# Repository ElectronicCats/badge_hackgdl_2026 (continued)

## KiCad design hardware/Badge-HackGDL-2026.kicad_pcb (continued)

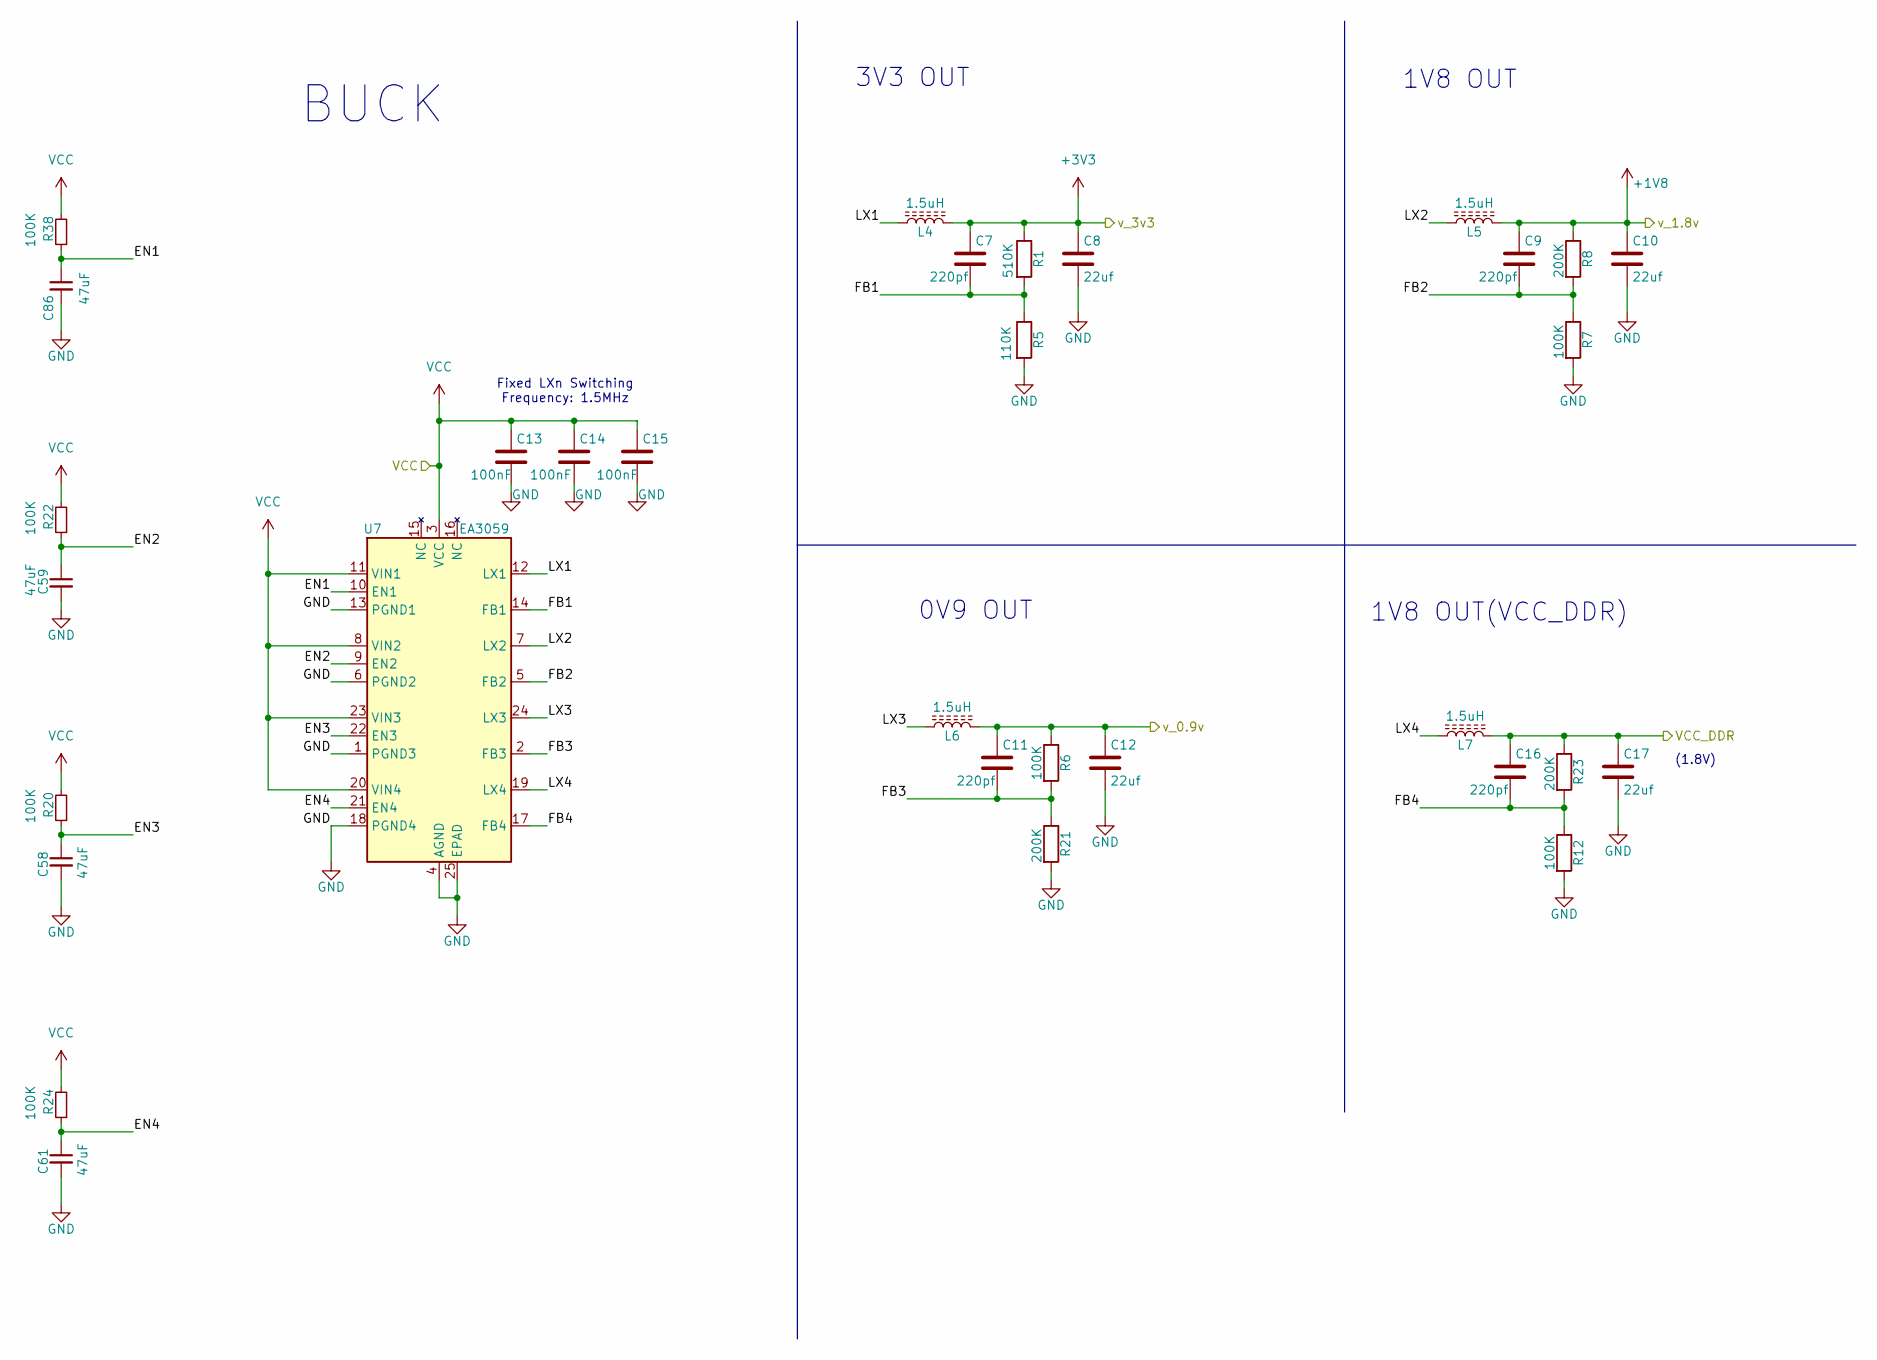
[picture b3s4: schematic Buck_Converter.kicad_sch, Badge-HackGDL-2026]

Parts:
C7, C9, C11, C16: 220pf; C_0402_1005Metric; LCSC# C107001
C8, C10, C12, C17: 22uf; C_0402_1005Metric; LCSC# C415703
C13, C14, C15: 100nF; C_0402_1005Metric; LCSC# C77020
C58, C59, C61, C86: 47uF; C_0603_1608Metric; LCSC# C140782
L4, L5, L6, L7: 1.5uH; L_1008_2520Metric; LCSC# C7427193
R1: 510K; R_0402_1005Metric; LCSC# C365024
R5: 110K; R_0402_1005Metric; LCSC# C2909311
R6, R7, R12, R20, R22, R24, R38: 100K; R_0402_1005Metric; LCSC# C844674
R8, R21, R23: 200K; R_0402_1005Metric; LCSC# C364966
U7: EA3059; VQFN-24-1EP_4x4mm_P0.5mm_EP2.5x2.5mm; LCSC# C111586

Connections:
+1V8: C9.1, C10.1, L5.2, R8.1; also elsewhere on the board
+3V3: C7.1, C8.1, L4.2, R1.1; also elsewhere on the board
/Buck_Converter/EN1: C86.1, R38.1, U7.10 (EN1)
/Buck_Converter/EN2: C59.1, R22.1, U7.9 (EN2)
/Buck_Converter/EN3: C58.1, R20.1, U7.22 (EN3)
/Buck_Converter/EN4: C61.1, R24.1, U7.21 (EN4)
/Buck_Converter/FB1: C7.2, R1.2, R5.1, U7.14 (FB1)
/Buck_Converter/FB2: C9.2, R7.1, R8.2, U7.5 (FB2)
/Buck_Converter/FB3: C11.2, R6.2, R21.1, U7.2 (FB3)
/Buck_Converter/FB4: C16.2, R12.1, R23.2, U7.17 (FB4)
/Buck_Converter/LX1: L4.1, U7.12 (LX1)
/Buck_Converter/LX2: L5.1, U7.7 (LX2)
/Buck_Converter/LX3: L6.1, U7.24 (LX3)
/Buck_Converter/LX4: L7.1, U7.19 (LX4)
/Buck_Converter/VCC_DDR: C16.1, C17.1, L7.2, R23.1; also elsewhere on the board
/MCU/VDD_ARM: C11.1, C12.1, L6.2, R6.1; also elsewhere on the board
GND: C8.2, C10.2, C12.2, C13.2, C14.2, C15.2, C17.2, C58.2, C59.2, C61.2, C86.2, R5.2, R7.2, R12.2, R21.2, U7.1 (PGND3), U7.4 (AGND), U7.6 (PGND2), U7.13 (PGND1), U7.18 (PGND4), U7.25 (EPAD); also elsewhere on the board
VCC: C13.1, C14.1, C15.1, R20.2, R22.2, R24.2, R38.2, U7.3 (VCC), U7.8 (VIN2), U7.11 (VIN1), U7.20 (VIN4), U7.23 (VIN3); also elsewhere on the board

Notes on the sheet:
Fixed LXn Switching Frequency: 1.5MHz
1V8 OUT(VCC_DDR)
1V8 OUT
(1.8V)
BUCK
0V9 OUT
3V3 OUT

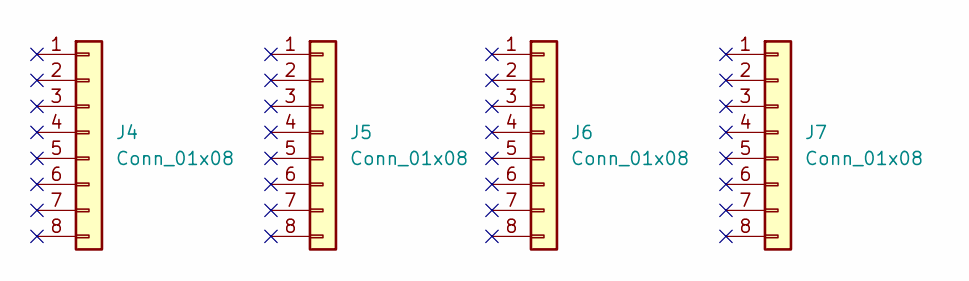
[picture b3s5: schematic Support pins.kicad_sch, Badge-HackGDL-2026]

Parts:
J4, J5, J6, J7: Conn_01x08; PinSocket_1x08_P2.54mm_Vertical; LCSC# C5224027

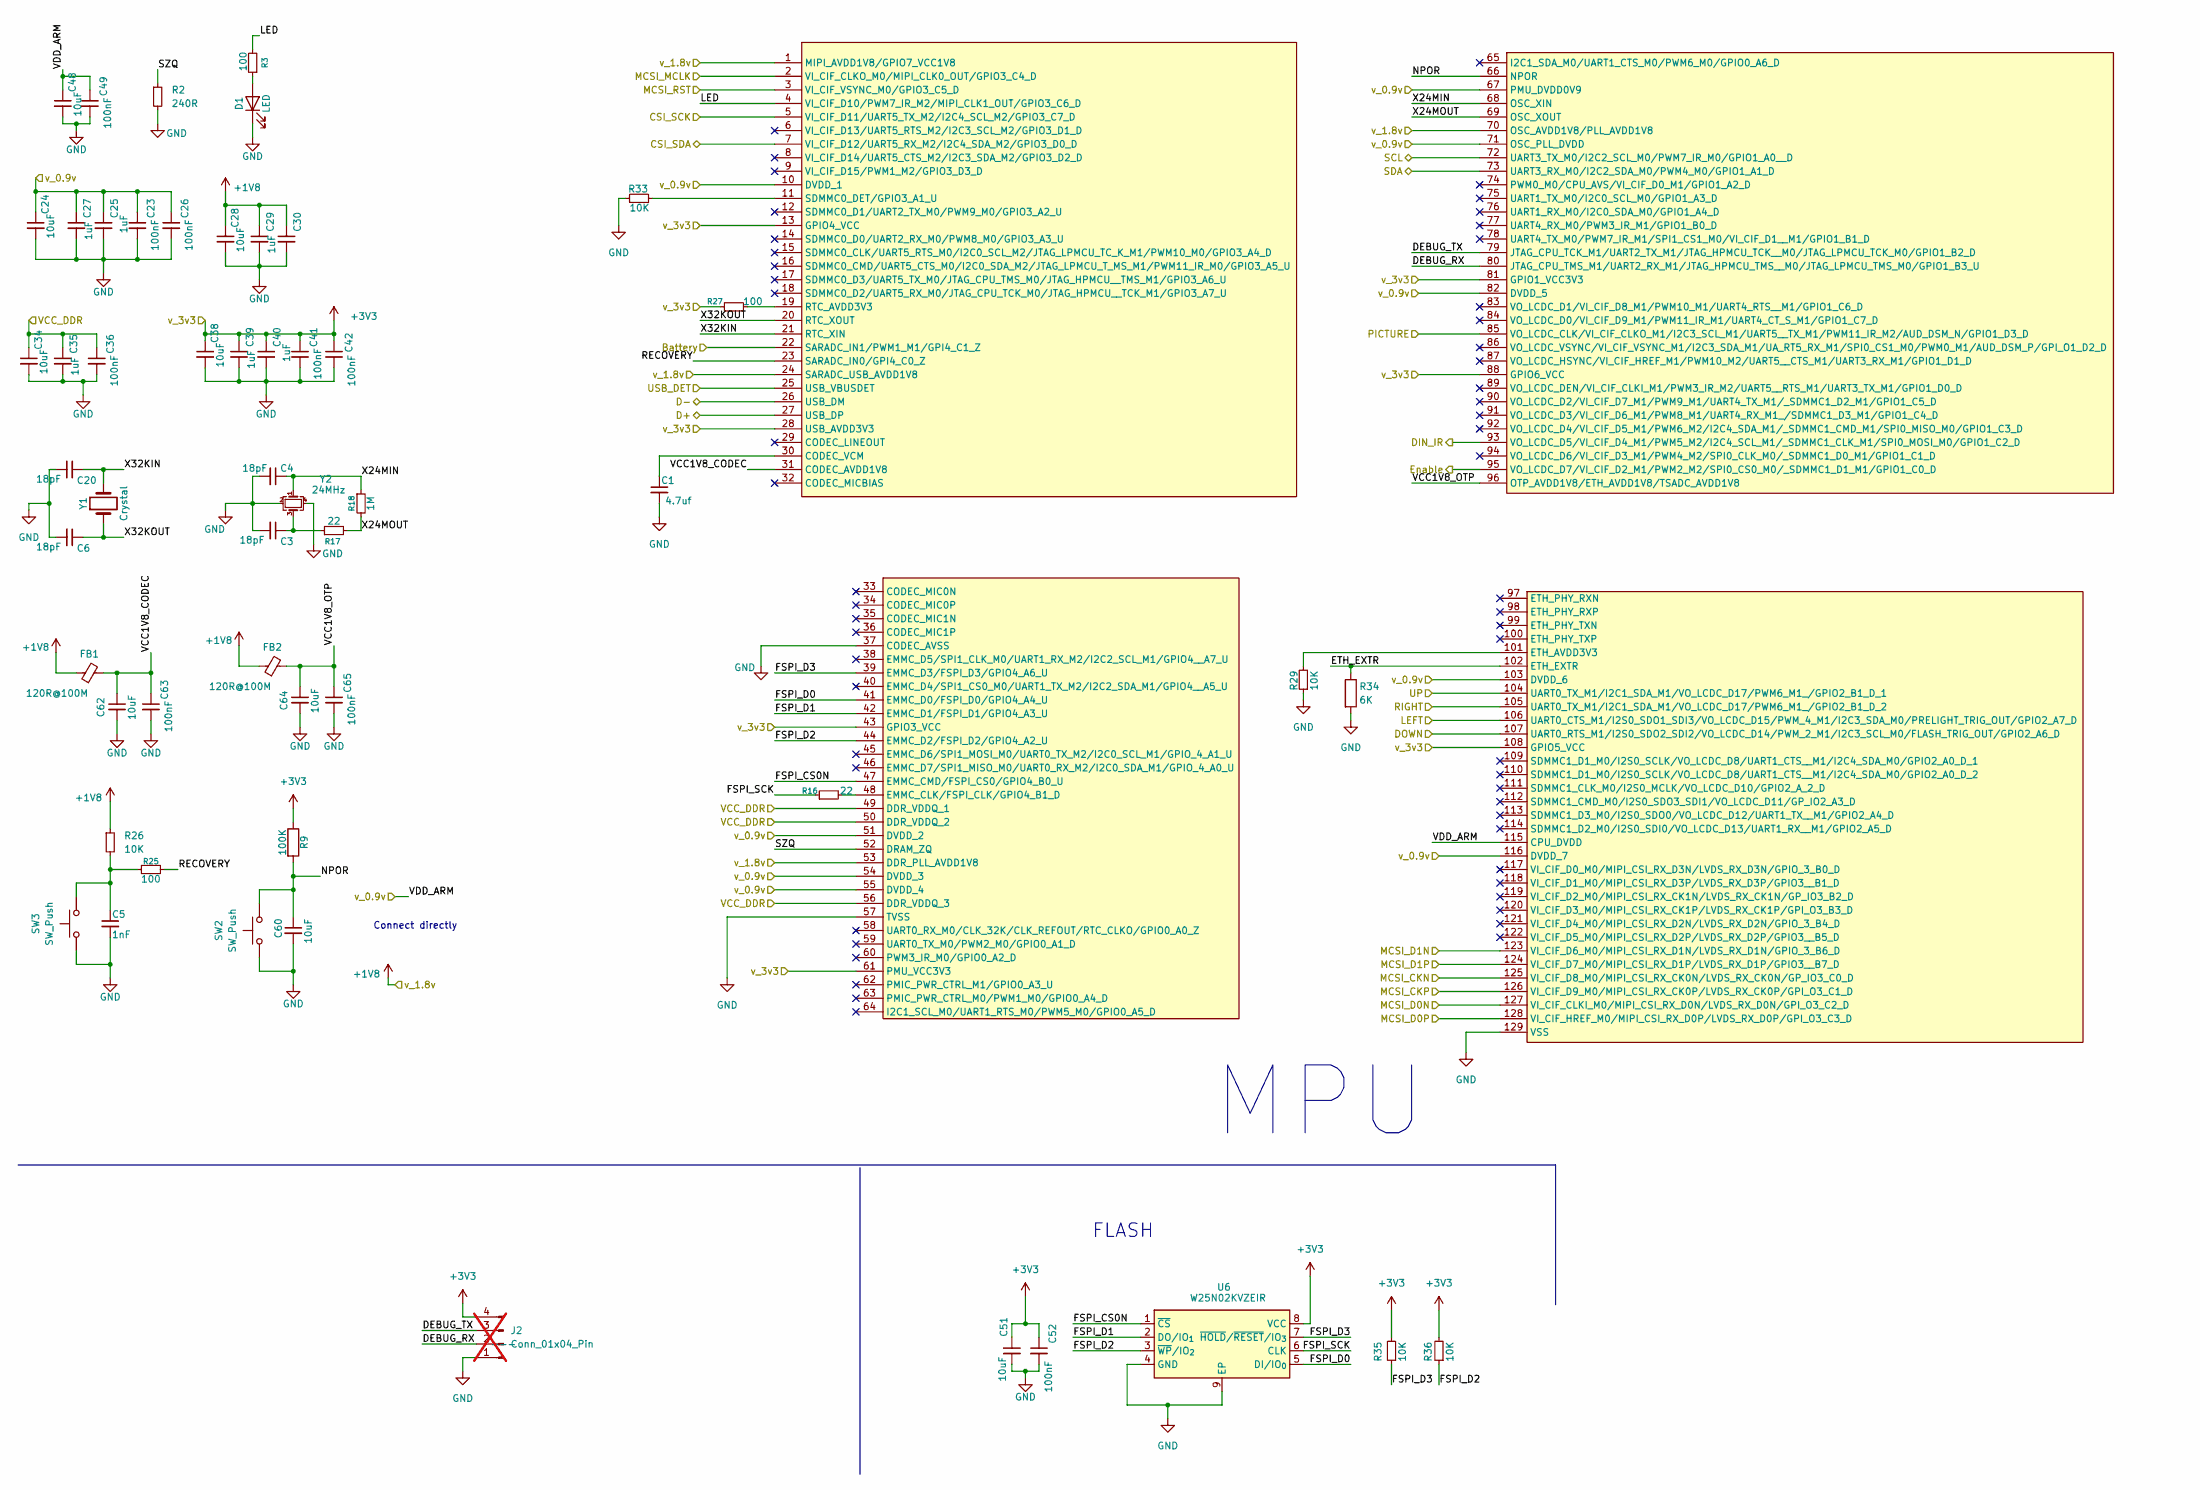
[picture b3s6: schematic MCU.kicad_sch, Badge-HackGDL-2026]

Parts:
C1: 4.7uf; C_0402_1005Metric; LCSC# C6119795
C3, C4, C6, C20: 18pF; C_0402_1005Metric; LCSC# C161534
C5: 1nF; C_0402_1005Metric; LCSC# C189467
C23, C26, C36, C41, C42, C49, C52, C63, C65: 100nF; C_0402_1005Metric; LCSC# C77020
C24, C28, C34, C38, C48, C51, C62, C64: 10uF; C_0402_1005Metric; LCSC# C7472949
C25, C27, C29, C30, C35, C39, C40: 1uF; C_0402_1005Metric; LCSC# C52923
C60: 10uF; C_0603_1608Metric; LCSC# C96446
D1: LED; LED_0603_1608Metric; LCSC# C22371297
FB1, FB2: 120R@100M; L_0603_1608Metric; LCSC# C14709
J2: Conn_01x04_Pin; 4 Pin 2.54mm; not fitted
R2: 240R; R_0402_1005Metric; LCSC# C25094
R3, R25, R27: 100; R_0402_1005Metric; LCSC# C2906860
R9: 100K; R_0402_1005Metric; LCSC# C844674
R16, R17: 22; R_0402_1005Metric; LCSC# C159964
R18: 1M; R_0402_1005Metric; LCSC# C131492
R26, R29, R33, R35, R36: 10K; R_0402_1005Metric; LCSC# C2759535
R34: 6K; R_0805_2012Metric; LCSC# C2828725
SW2, SW3: SW_Push; SW_SPST_TL3342; LCSC# C318889
U6: W25N02KVZEIR; WSON-8-1EP_8x6mm_P1.27mm_EP3.4x4.3mm; LCSC# C3010298
U8: RV1106G3; LCSC# C5328706
Y1: Crystal; Crystal_SMD_3215-2Pin_3.2x1.5mm; LCSC# C620155
Y2: 24MHz; Crystal_SMD_3225-4Pin_3.2x2.5mm; LCSC# C70590

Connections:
+1V8: C28.1, C29.1, C30.1, FB1.1, FB2.1, R26.1, U8.1 (MIPI_AVDD1V8/GPIO7_VCC1V8), U8.24 (SARADC_USB_AVDD1V8), U8.53 (DDR_PLL_AVDD1V8), U8.70 (OSC_AVDD1V8/PLL_AVDD1V8); also elsewhere on the board
+3V3: C38.1, C39.1, C40.1, C41.1, C42.1, C51.1, C52.1, J2.4, R9.1, R27.1, R35.2, R36.2, U6.8 (VCC), U8.13 (GPIO4_VCC), U8.28 (USB_AVDD3V3), U8.43 (GPIO3_VCC), U8.61 (PMU_VCC3V3), U8.81 (GPIO1_VCC3V3), U8.88 (GPIO6_VCC), U8.108 (GPIO5_VCC); also elsewhere on the board
/Buck_Converter/VCC_DDR: C34.1, C35.1, C36.1, U8.49 (DDR_VDDQ_1), U8.50 (DDR_VDDQ_2), U8.56 (DDR_VDDQ_3); also elsewhere on the board
/Cam/CSI_SCK: U8.5 (VI_CIF_D11/UART5_TX_M2/I2C4_SCL_M2/GPIO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); also elsewhere on the board
/Cam/CSI_SDA: U8.7 (VI_CIF_D12/UART5_RX_M2/I2C4_SDA_M2/GPIO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); also elsewhere on the board
/Cam/MCSI_CKN: U8.125 (VI_CIF_D8_M0/MIPI_CSI_RX_CK0N/LVDS_RX_C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); also elsewhere on the board
/Cam/MCSI_CKP: U8.126 (VI_CIF_D9_M0/MIPI_CSI_RX_CK0P/LVDS_RX_C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); also elsewhere on the board
/Cam/MCSI_D0N: U8.127 (VI_CIF_CLKI_M0/MIPI_CSI_RX_D0N/LVDS_RX_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); also elsewhere on the board
/Cam/MCSI_D0P: U8.128 (VI_CIF_HREF_M0/MIPI_CSI_RX_D0P/LVDS_RX_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); also elsewhere on the board
/Cam/MCSI_D1N: U8.123 (VI_CIF_D6_M0/MIPI_CSI_RX_D1N/LVDS_RX_D1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); also elsewhere on the board
/Cam/MCSI_D1P: U8.124 (VI_CIF_D7_M0/MIPI_CSI_RX_D1P/LVDS_RX_D1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); also elsewhere on the board
/Cam/MCSI_MCLK: U8.2 (VI_CIF_CLKO_M0/MIPI_CLK0_OUT/GPIO3_C4_D); also elsewhere on the board
/Cam/MCSI_RST: U8.3 (VI_CIF_VSYNC_M0/GPIO3_C5_D); also elsewhere on the board
/MCU/Battery: U8.22 (SARADC_IN1/PWM1_M1/GPI4_C1_Z); also elsewhere on the board
/MCU/D+: U8.27 (USB_DP); also elsewhere on the board
/MCU/D-: U8.26 (USB_DM); also elsewhere on the board
/MCU/DEBUG_RX: J2.2, U8.80 (JTAG_CPU_TMS_M1/UART2_RX_M1/JTAG_HPMCU_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)
/MCU/DEBUG_TX: J2.3, U8.79 (JTAG_CPU_TCK_M1/UART2_TX_M1/JTAG_HPMCU_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)
/MCU/DIN_IR: U8.93 (VO_LCDC_D5/VI_CIF_D4_M1/PWM5_M2/I2C4_SC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); also elsewhere on the board
/MCU/DOWN: U8.107 (UART0_RTS_M1/I2S0_SDO2_SDI2/VO_LCDC_D14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); also elsewhere on the board
/MCU/ETH_EXTR: R34.1, U8.102 (ETH_EXTR)
/MCU/Enable: U8.95 (VO_LCDC_D7/VI_CIF_D2_M1/PWM2_M2/SPI0_CS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); also elsewhere on the board
/MCU/FSPI_CS0N: U6.1 (~CS), U8.47 (EMMC_CMD/FSPI_CS0/GPIO4_B0_U)
/MCU/FSPI_D0: U6.5 (DI/IO_{0}), U8.41 (EMMC_D0/FSPI_D0/GPIO4_A4_U)
/MCU/FSPI_D1: U6.2 (DO/IO_{1}), U8.42 (EMMC_D1/FSPI_D1/GPIO4_A3_U)
/MCU/FSPI_D2: R36.1, U6.3 (~WP/IO_{2}), U8.44 (EMMC_D2/FSPI_D2/GPIO4_A2_U)
/MCU/FSPI_D3: R35.1, U6.7 (~HOLD/~RESET/IO_{3}), U8.39 (EMMC_D3/FSPI_D3/GPIO4_A6_U)
/MCU/FSPI_SCK: R16.1, U6.6 (CLK)
/MCU/LED: R3.2, U8.4 (VI_CIF_D10/PWM7_IR_M2/MIPI_CLK1_OUT/GPI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)
/MCU/LEFT: U8.106 (UART0_CTS_M1/I2S0_SDO1_SDI3/VO_LCDC_D15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); also elsewhere on the board
/MCU/NPOR: C60.1, R9.2, SW2.2, U8.66 (NPOR)
/MCU/PICTURE: U8.85 (VO_LCDC_CLK/VI_CIF_CLKO_M1/I2C3_SCL_M1/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); also elsewhere on the board
/MCU/RECOVERY: R25.2, U8.23 (SARADC_IN0/GPI4_C0_Z)
/MCU/RIGHT: U8.105 (UART0_TX_M1/I2C1_SDA_M1/VO_LCDC_D17/PWM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); also elsewhere on the board
/MCU/SCL: U8.72 (UART3_TX_M0/I2C2_SCL_M0/PWM7_IR_M0/GPIO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); also elsewhere on the board
/MCU/SDA: U8.73 (UART3_RX_M0/I2C2_SDA_M0/PWM4_M0/GPIO1_A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); also elsewhere on the board
/MCU/SZQ: R2.1, U8.52 (DRAM_ZQ)
/MCU/UP: U8.104 (UART0_TX_M1/I2C1_SDA_M1/VO_LCDC_D17/PWM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); also elsewhere on the board
/MCU/USB_DET: U8.25 (USB_VBUSDET); also elsewhere on the board
/MCU/VCC1V8_CODEC: C62.1, C63.1, FB1.2, U8.31 (CODEC_AVDD1V8)
/MCU/VCC1V8_OTP: C64.1, C65.1, FB2.2, U8.96 (OTP_AVDD1V8/ETH_AVDD1V8/TSADC_AVDD1V8)
/MCU/VDD_ARM: C23.1, C24.1, C25.1, C26.1, C27.1, C48.1, C49.1, U8.10 (DVDD_1), U8.51 (DVDD_2), U8.54 (DVDD_3), U8.55 (DVDD_4), U8.67 (PMU_DVDD0V9), U8.71 (OSC_PLL_DVDD), U8.82 (DVDD_5), U8.103 (DVDD_6), U8.115 (CPU_DVDD), U8.116 (DVDD_7); also elsewhere on the board
/MCU/X24MIN: C4.1, R18.1, U8.68 (OSC_XIN), Y2.1
/MCU/X24MOUT: R17.2, R18.2, U8.69 (OSC_XOUT)
/MCU/X32KIN: C20.1, U8.21 (RTC_XIN), Y1.2
/MCU/X32KOUT: C6.1, U8.20 (RTC_XOUT), Y1.1
GND: C1.2, C3.2, C4.2, C5.2, C6.2, C20.2, C23.2, C24.2, C25.2, C26.2, C27.2, C28.2, C29.2, C30.2, C34.2, C35.2, C36.2, C38.2, C39.2, C40.2, C41.2, C42.2, C48.2, C49.2, C51.2, C52.2, C60.2, C62.2, C63.2, C64.2, C65.2, D1.1 (K), J2.1, R2.2, R29.1, R33.1, R34.2, SW2.1, SW3.1, U6.4 (GND), U6.9 (EP), U8.37 (CODEC_AVSS), U8.57 (TVSS), U8.129 (VSS), Y2.2, Y2.4; also elsewhere on the board
unnamed: C3.1, R17.1, Y2.3
unnamed: C5.1, R25.1, R26.2, SW3.2
unnamed: D1.2 (A), R3.1
unnamed: C1.1, U8.30 (CODEC_VCM)
unnamed: R27.2, U8.19 (RTC_AVDD3V3)
unnamed: R33.2, U8.11 (SDMMC0_DET/GPIO3_A1_U)
unnamed: R16.2, U8.48 (EMMC_CLK/FSPI_CLK/GPIO4_B1_D)
unnamed: R29.2, U8.101 (ETH_AVDD3V3)

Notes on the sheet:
FLASH
Connect directly
MPU

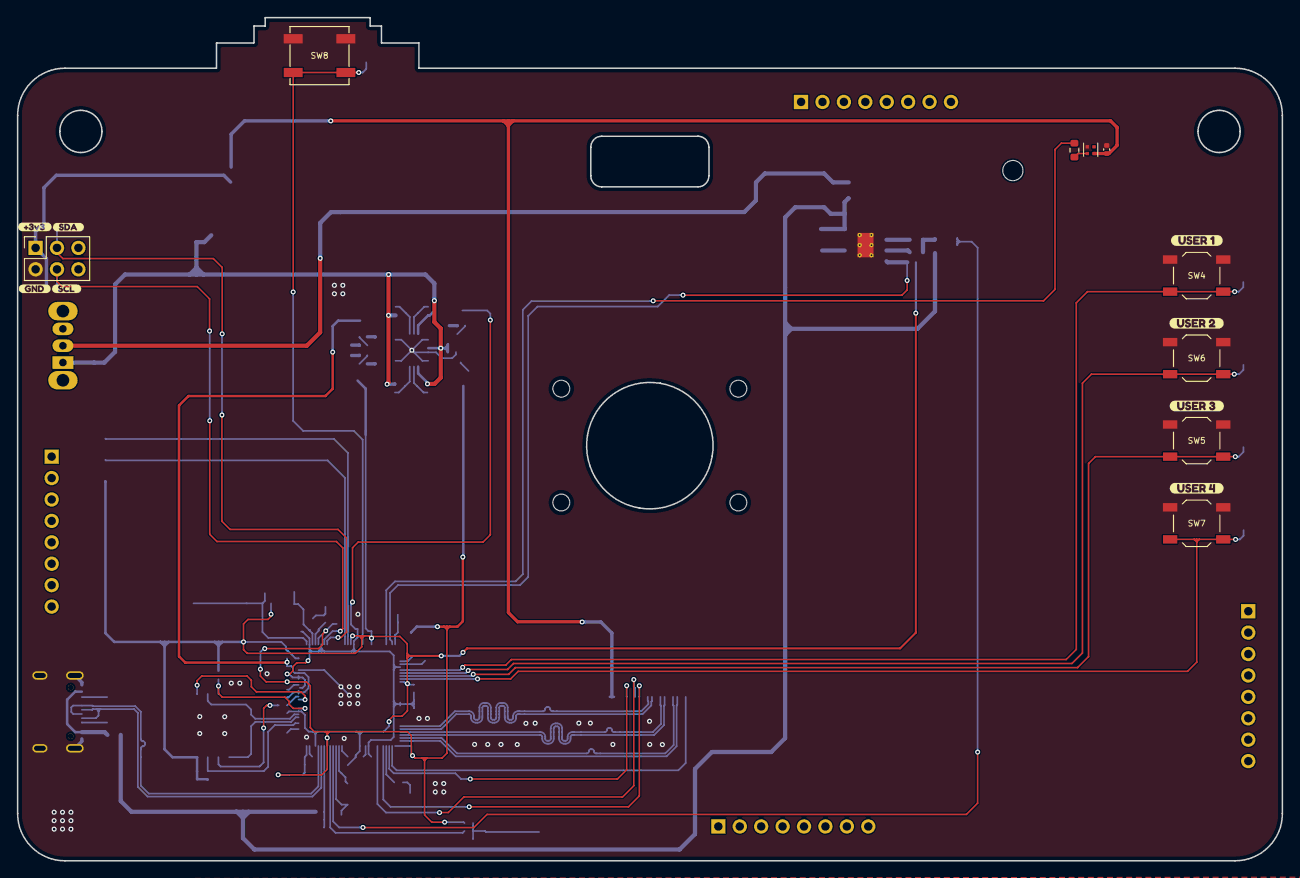
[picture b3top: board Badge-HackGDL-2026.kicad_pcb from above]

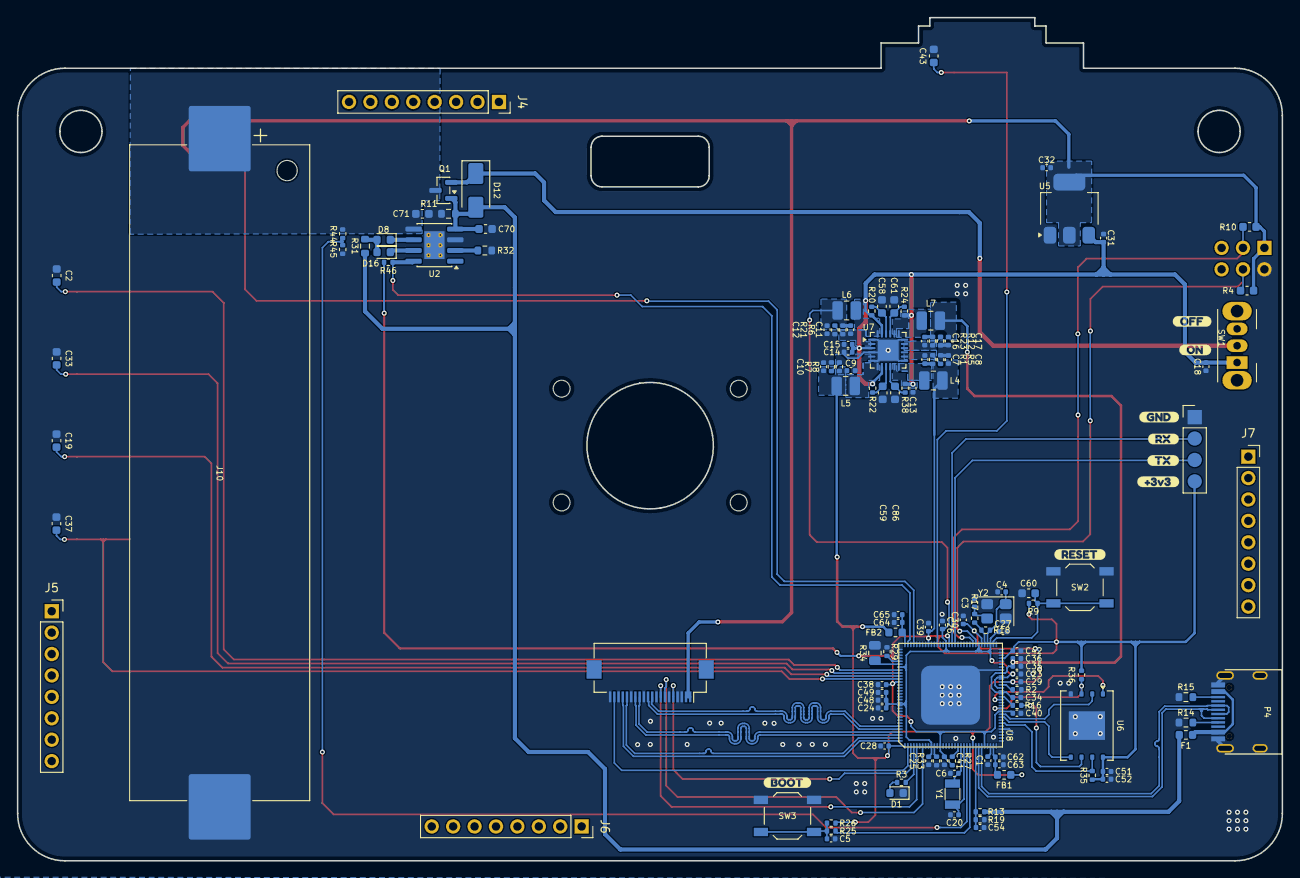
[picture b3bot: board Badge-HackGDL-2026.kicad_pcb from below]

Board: 2 copper layers, 150.0 x 100.0 mm, 151 parts (133 on the bottom side), 80 nets.

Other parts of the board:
kibuzzard-684B03BD: G***; kibuzzard-684B03BD
kibuzzard-684B03C9: G***; kibuzzard-684B03C9
kibuzzard-684B03D5: G***; kibuzzard-684B03D5
kibuzzard-69714B9C: G***; kibuzzard-69714B9C
kibuzzard-69714BBC: G***; kibuzzard-69714BBC
kibuzzard-69714BDE: G***; kibuzzard-69714BDE
kibuzzard-69714C02: G***; kibuzzard-69714C02
kibuzzard-69714C5E: G***; kibuzzard-69714C5E
kibuzzard-69714C72: G***; kibuzzard-69714C72
kibuzzard-69714C98: G***; kibuzzard-69714C98
kibuzzard-69714CA0: G***; kibuzzard-69714CA0
kibuzzard-6892465C: G***; kibuzzard-6892465C
kibuzzard-6971487E: G***; kibuzzard-6971487E
kibuzzard-6971488E: G***; kibuzzard-6971488E
kibuzzard-69714845: G***; kibuzzard-69714845
kibuzzard-69714866: G***; kibuzzard-69714866

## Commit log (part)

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2025-12-17 feat(Hw):Init_Schematic
2025-12-19 feat(Hw):Update_Schematic_And_BOM
2025-12-23 feat(Hw):Update_Schematic_And_Floorplan
2025-12-23 feat(Hw):Update_Schematic
2026-01-06 feat(Hw):Update_Floorplan_And_Route
2026-01-07 feat(Hw):Update_Route
2026-01-12 feat(Hw):Update_Route_Init_Rear_Board
2026-01-13 feat(Hw):Update_Schematic_And_Route
2026-01-14 feat(Hw):Update_Rear_Board
2026-01-15 feat(Hw):Update_3Dmodels_And_Rear_Board
2026-01-15 feat(Hw):Update_Shematic_And_PCB
2026-01-21 feat(Hw):Update_BOM
2026-01-21 feat(Hw):Update_Labels
2026-01-28 feat(Hw):Init_Schematic_And_Floorplan
2026-01-29 feat(Hw):Update_Route_And_Init_Addon_Tortuguita
2026-02-13 feat(fw): Add luckfox-sdk
2026-02-19 feat(fw): Fix luckfox-adk
2026-02-19 feat: add submodule luckfox-pico
2026-03-04 feat: update submodule luckfox-pico
2026-03-06 feat: Update readme
2026-03-10 feat(Fw):Init_Firmware_Addon_Tortuguita
2026-03-10 feat(Fw):Init_Firmware_Addon_Pescadito
2026-03-13 feat(Fw):Update_Firmware_Addon_Pescadito
2026-04-30 feat: Update submodule luckfox-pico sdk
2026-05-19 Adds startup and capture LED indicators
    Implements visual feedback using the NeoPixel for key system events.
    A green blink sequence confirms successful device startup, providing a clear initialization signal.
    A white blink sequence is triggered when the capture button (`KEY_ENTER`) is pressed, signaling that a photo has been taken. This uses an atomic flag (`sig_atomic_t`) for safe inter-thread communicat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
